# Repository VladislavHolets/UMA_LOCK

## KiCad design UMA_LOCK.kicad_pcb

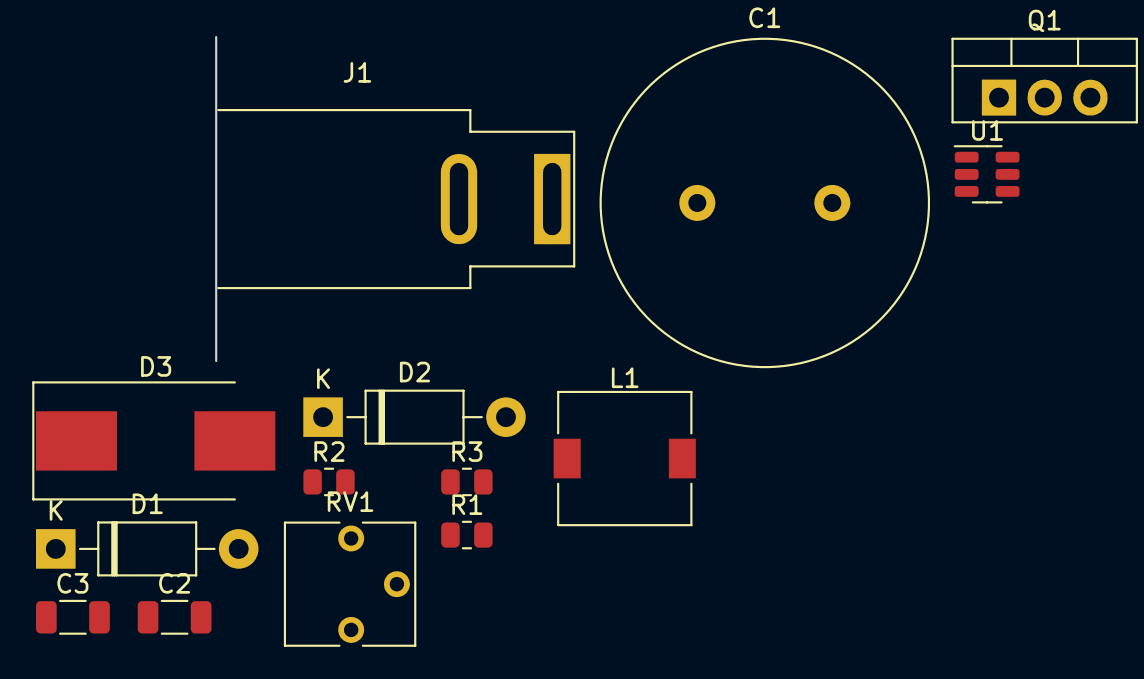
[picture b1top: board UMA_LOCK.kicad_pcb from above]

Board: 2 copper layers, 14 parts (0 on the bottom side), 10 nets, no tracks yet.

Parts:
C1: 4700x25; C_Radial_D18.0mm_H35.5mm_P7.50mm
C2, C3: 10uF; C_1206_3216Metric
D1, D2: 1N4004; D_DO-41_SOD81_P10.16mm_Horizontal
D3: SS34; D_SMC_Handsoldering
J1: Jack-DC; BarrelJack_SwitchcraftConxall_RAPC10U_Horizontal
L1: 22uH; L_7.3x7.3_H4.5
Q1: IRLB8721PBF; TO-220-3_Vertical
R1: 400; R_0805_2012Metric
R2: 500; R_0805_2012Metric
R3: 2K2; R_0805_2012Metric
RV1: 100K; Potentiometer_Vishay_T73YP_Vertical
U1: MT3608; SOT-23-6

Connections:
+12V: C3.1, D3.1 (K), R1.1, RV1.1
GND: C1.2, C2.2, C3.2, Q1.3 (S), R3.2, U1.2 (GND)
unnamed: C1.1, D1.1 (K), D2.1 (K), J1.1
unnamed: D1.2 (A), J1.2, Q1.2 (D)
unnamed: D2.2 (A), R1.2
unnamed: D3.2 (A), L1.2, U1.1 (SW)
unnamed: Q1.1 (G), R2.1
unnamed: R3.1, RV1.3
unnamed: RV1.2, U1.3 (FB)
VCC: C2.1, L1.1, U1.5 (IN)

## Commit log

2022-04-21 initial_commit
